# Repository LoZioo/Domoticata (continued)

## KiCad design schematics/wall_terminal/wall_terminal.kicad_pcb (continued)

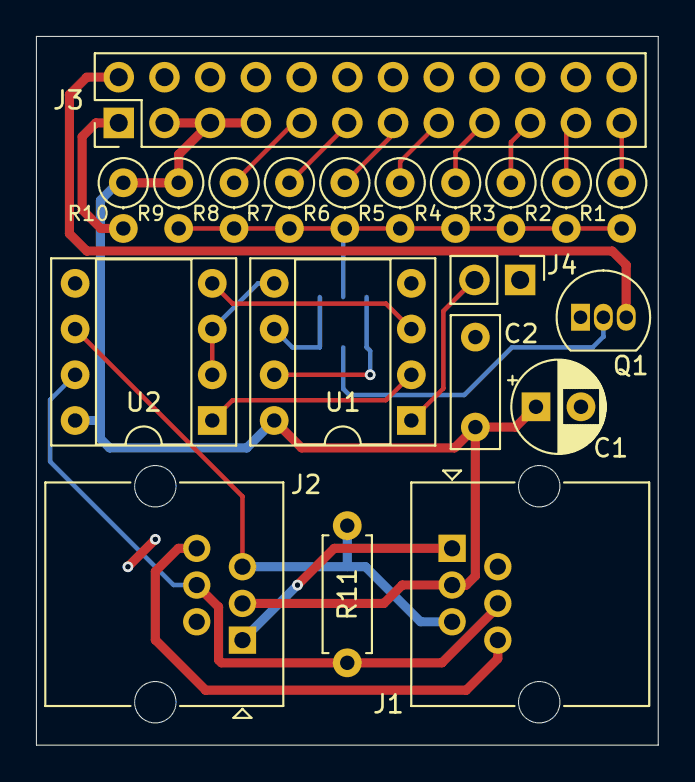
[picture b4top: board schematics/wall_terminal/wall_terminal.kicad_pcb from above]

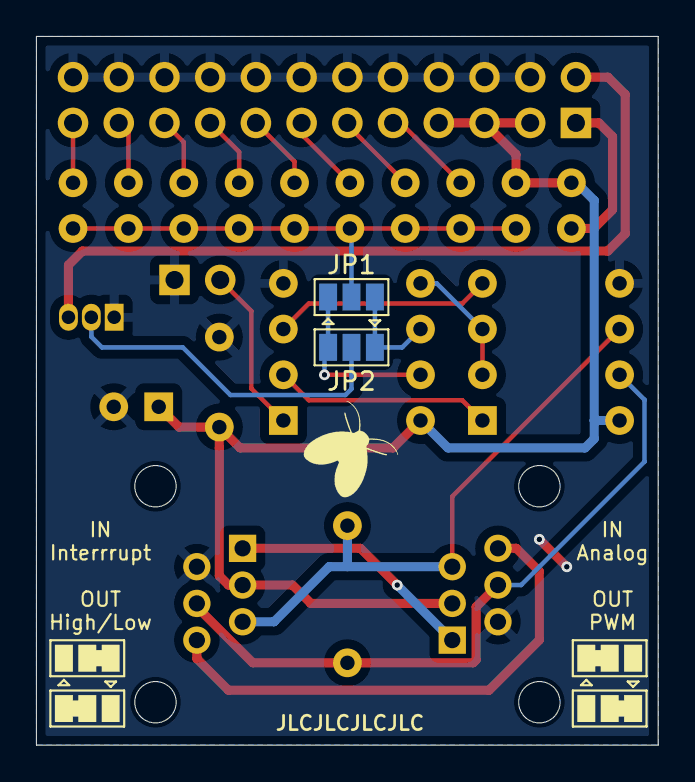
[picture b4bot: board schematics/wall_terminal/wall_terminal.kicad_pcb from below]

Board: 2 copper layers, 34.5 x 39.4 mm, 22 parts (2 on the bottom side), 24 nets.

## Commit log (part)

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2024-07-29 feat: added minimal button states library.
2024-07-29 feat
2024-07-29 chore
2024-07-29 docs
2024-07-29 feat: first working library code.
2024-07-30 feat: improved the `ul_utils_delay_nonblock()` function.
2024-07-30 feat: remove some static variables to free space.
2024-07-30 chore: removed dup library.
2024-07-30 feat: first working code.
2024-07-31 fix: forced to output the uart pins
2024-07-31 chore: splitted variable and const configurations.
2024-07-31 feat: added rx and tx IDs
2024-07-31 fix: bit encoding.
2024-07-31 feat: added multiple preprocessors if.
2024-08-02 feat: dynamic size typing.
2024-08-02 refactor
2024-08-03 !feat: added CRC8.
2024-08-03 feat: code boilerplate.
2024-08-03 chore: changed baudrate to 921600
2024-08-03 chore: updated sdkconfig
2024-08-03 !feat: added UniLibC libraries.
2024-08-03 chore: code boilerplate
2024-08-03 chore: setup Kconfig.projbuild
2024-08-03 feat: GPIO_setup()
2024-08-03 feat: UART_setup()
2024-08-03 chore: freertos scheduler to 1khz
2024-08-03 feat: first UART_poll() implementation
2024-08-04 feat: first RS-485 working code.
2024-08-04 !feat
2024-08-06 feat: begin thread oriented implementation.
2024-08-06 feat: delay to stabilize the peripherals
2024-08-06 feat: ledc initialization
2024-08-06 feat: fade function test code
2024-08-06 !feat: pwm fade test code.
2024-08-07 refactor: thread spawn method
2024-08-07 chore(Kconfig.projbuild)
2024-08-07 feat: adc test code
2024-08-08 feat: first ADC working test code.
2024-08-08 feat: delay_remainings()
2024-08-08 chore: added ul_pm.h
2024-08-09 feat: removed debug code.
2024-08-10 chore: added optimal voltage divider resistor's values.
2024-08-11 !feat: dropped analog buttons in favour of digital buttons and trimmer.
2024-08-11 feat: fast digital read
2024-08-11 !feat: final firmware.
2024-08-11 !feat: situational hardware configurations.
2024-08-12 chore: button test code.
2024-08-12 refactor: `rs485_task()`.
2024-08-12 refactor: `pm_task()`.
2024-08-12 refactor: `pwm_task()`.
2024-08-12 fix: `pwm_write()`.
2024-08-12 feat: button map first code.
2024-08-12 !feat: `handle_button_press()`.
2024-08-12 !feat: `handle_trimmer_change()`.
2024-08-12 feat: `led_gamma_correction()` first test function.
2024-08-16 feat: added PowerMonitor resistor's values.
2024-08-16 feat: screw to fuse-
2024-08-17 feat: optimized size of `pwm_data_t`.
2024-08-17 chore: `pwm_led_gamma_correction`
2024-08-17 refactor: project structure
2024-08-17 !refactor
2024-08-18 !refactor: project structure.
2024-08-18 feat: initialization assert
2024-08-18 feat: added single tasks configuration on menuconfig.
2024-08-18 chore: removed `PWM_BIT_RES` from Kconfig.
2024-08-18 feat: base keymap
2024-08-18 feat: multi zone buttons optimization.
2024-08-18 feat: removed turning on light with trimmers.
2024-08-18 chore: ready to adapt the sample format to the ul_pm library.
2024-08-19 fix: ADC attenuation.
2024-08-19 fix: powermonitor lower resistor to 680ohm
2024-08-19 feat: adc max value instead of adc bit resolution.
2024-08-19 chore: code optimization.
2024-08-20 !feat: added sampling frequency calculator section.
2024-08-20 feat: dynamic sample index offset.
2024-08-20 !feat: first powermonitor working code.
2024-08-22 feat: hardware configurations.
2024-08-22 chore: disabled powermonitor.
2024-08-22 feat: log stub for rs485.
2024-08-23 feat: mapped zones.
2024-08-24 feat: log stubs
2024-08-24 chore: device id format.
2024-08-24 chore: log
2024-08-28 feat: wifi support
2024-08-28 chore: 'Enable Multi Band Operation Certification Support' to support many SSID with different channels covering the same area.
2024-08-28 chore: maxed flash and cpu frequencies.
2024-08-29 refactor: task notification instead of binary semaphore.
2024-08-29 chore: ota partition table.
2024-08-29 feat: added emergency switches schematics.
2024-08-30 feat: ota code boilerplate.
2024-08-30 feat: first ota test code.
2024-08-30 feat: various APIs.
2024-08-30 feat: wifi preliminar checks.
2024-08-30 chore: ota test code.
2024-08-30 !fix
2024-08-30 feat: ota firmware update Kconfig configurations.
2024-08-30 chore: added fs to partition table.
2024-08-31 !feat: soft ap
2024-08-31 chore: kconfig wifi soft ap settings.
2024-09-02 chore: added button state log.
2024-09-06 chore: fs code boilerplate.
2024-09-06 chore: added littlefs component.
2024-09-06 feat: littlefs initialization.
2024-09-06 feat: `fs_available()`
2024-09-06 feat: littlefs python flash script
2024-09-06 refactor: moved NVS code to dedicated library.
2024-09-06 chore: two fs partitions.
2024-09-06 feat: first nvs fs code.
2024-09-07 feat: fs demo code.
2024-09-07 feat: `nvs_new_handle()`
2024-09-07 !feat: wifi provisioning.
2024-09-08 temp commit
2024-09-08 !feat: API changed.
2024-09-09 refactor: less goto statements.
2024-09-09 fix: esp_err_t ret __attribute__((unused))
2024-09-09 feat: `fs_partition_write_unmounted()`
2024-09-09 feat: `fs_partition_unmounted_get_sha256()`
2024-09-09 !feat: fs ota
2024-09-09 !feat: final ota code.
2024-09-09 feat: webserver code boilerplate.
2024-09-10 feat: `gpio_write()`
2024-09-10 chore: wall terminals 6 and 8
2024-09-11 chore: led test.
2024-09-12 chore: removed trimmer from ID 6 and 8.
2024-09-12 chore: webserver configurations.
2024-09-12 feat: http server example.
2024-09-12 feat: first webserver example
2024-09-12 chore: snprintf instead of sprintf.
2024-09-13 feat: `__list_webserver_files_rec()` test.
2024-09-13 feat: linked list test.
2024-09-14 chore: linked list test.
2024-09-14 feat: now using `ul_errors_to_esp_err()`.
2024-09-14 !feat: littlefs webserver.
2024-09-14 feat: added `private.h`.
2024-09-14 feat: `webserver_reload()`.
2024-09-14 feat: MIME type from file type.
2024-09-15 feat: `__decode_uri()`
2024-09-16 chore: `format_if_mount_failed` to true.
2024-09-16 chore: `OTA_IPV4_ADDR_STR_LEN`
2024-09-16 chore: dynamic ota buffer.
2024-09-16 chore: `WIFI_IPV4_ADDR_STR_LEN`.
2024-09-16 feat: `__route_ota_update()`.
2024-09-16 !fix: `sizeof(buffer)` doesn't work on malloc buffers.
2024-09-16 chore: worker settings.
2024-09-16 !feat: async OTA thread.
2024-09-16 feat: new partition table.
2024-09-16 chore: tasks parameters.
2024-09-17 !refactor: removed OTA capabilities.
2024-09-17 feat: fan start up.
2024-09-17 feat: "/pm" route.
2024-09-17 feat: webserver files.
2024-09-17 chore: tuned correction factors.
2024-09-17 chore: adjusted `ESP_SYSTEM_PANIC` on menuconfig.
2024-09-18 feat: alarm support.
2024-09-18 feat: fan startup.
2025-04-24 feat: startup routine.
2025-04-24 chore: zone_t instead of uint8_t in pwm_write_zone()
